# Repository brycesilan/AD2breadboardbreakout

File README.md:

# AD2 Breadboard Breakout

This is a breadboard breakout for the Analog Discovery 2™ from Digitlent. Please don't sue me I just wanted to make my own version for cheap and share it with others.

I ordered my boards from JLC PCB with their 5 2 Layer Boards for $2.

I also ordered the headers from LCSC 
Male Header Part #: C124373
Female Header Part #: C124408
(I have't verified that these work yet)

## Contributing
Pull requests are welcome. Please let me know any ideas you have on impoving this board.

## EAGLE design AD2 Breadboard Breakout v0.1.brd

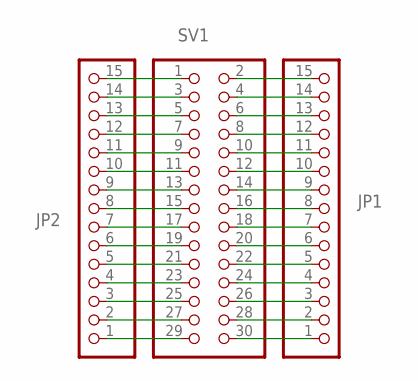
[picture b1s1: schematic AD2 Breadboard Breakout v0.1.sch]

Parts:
JP1, JP2: PINHD-1X15-CB; 1X15-CB
SV1: PINHD-2X15; 2X15

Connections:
unnamed: JP2.15, SV1.1
unnamed: JP1.15, SV1.2
unnamed: JP2.14, SV1.3
unnamed: JP1.14, SV1.4
unnamed: JP2.13, SV1.5
unnamed: JP1.13, SV1.6
unnamed: JP2.12, SV1.7
unnamed: JP1.12, SV1.8
unnamed: JP2.11, SV1.9
unnamed: JP1.11, SV1.10
unnamed: JP2.10, SV1.11
unnamed: JP1.10, SV1.12
unnamed: JP2.9, SV1.13
unnamed: JP1.9, SV1.14
unnamed: JP2.8, SV1.15
unnamed: JP1.8, SV1.16
unnamed: JP2.7, SV1.17
unnamed: JP1.7, SV1.18
unnamed: JP2.6, SV1.19
unnamed: JP1.6, SV1.20
unnamed: JP2.5, SV1.21
unnamed: JP1.5, SV1.22
unnamed: JP2.4, SV1.23
unnamed: JP1.4, SV1.24
unnamed: JP2.3, SV1.25
unnamed: JP1.3, SV1.26
unnamed: JP2.2, SV1.27
unnamed: JP1.2, SV1.28
unnamed: JP2.1, SV1.29
unnamed: JP1.1, SV1.30

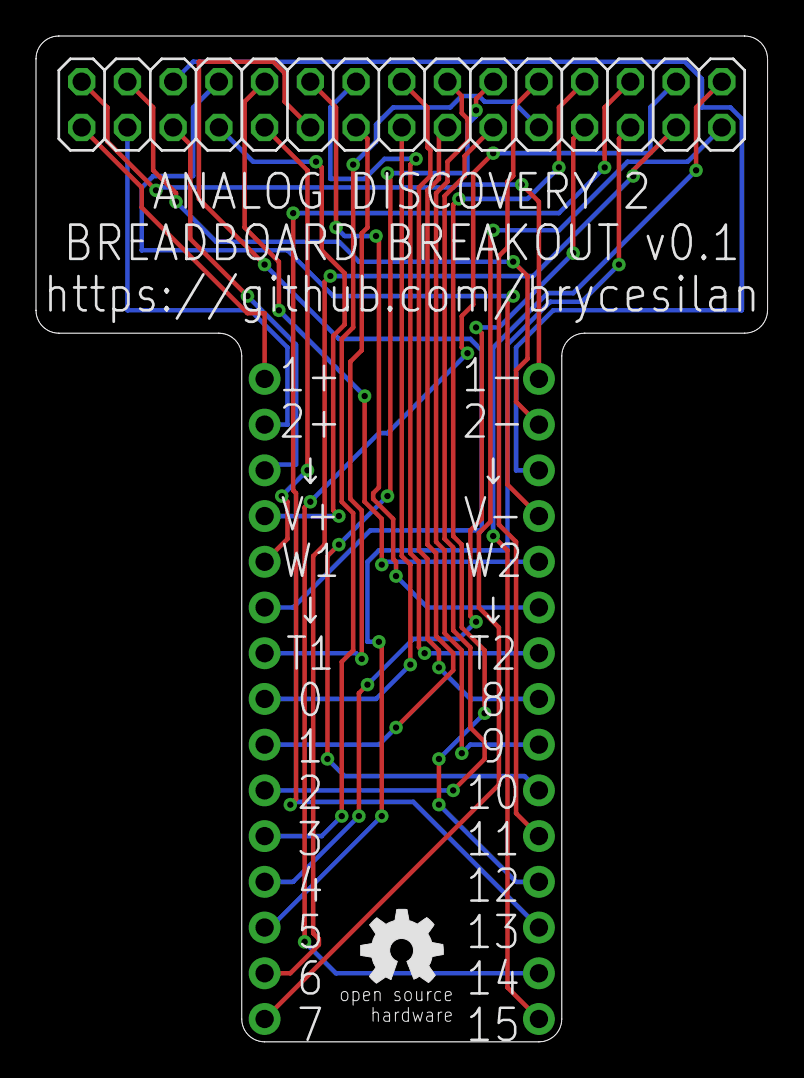
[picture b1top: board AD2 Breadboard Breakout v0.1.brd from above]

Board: 2 copper layers, 40.6 x 55.9 mm, 4 parts (0 on the bottom side), 30 nets.

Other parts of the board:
U$1: OSHW_5MM
